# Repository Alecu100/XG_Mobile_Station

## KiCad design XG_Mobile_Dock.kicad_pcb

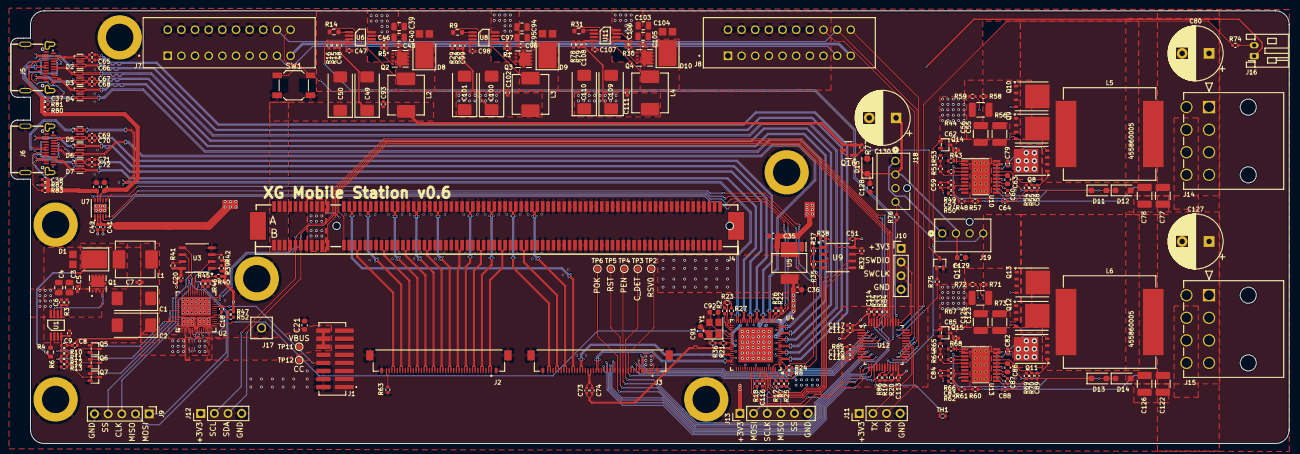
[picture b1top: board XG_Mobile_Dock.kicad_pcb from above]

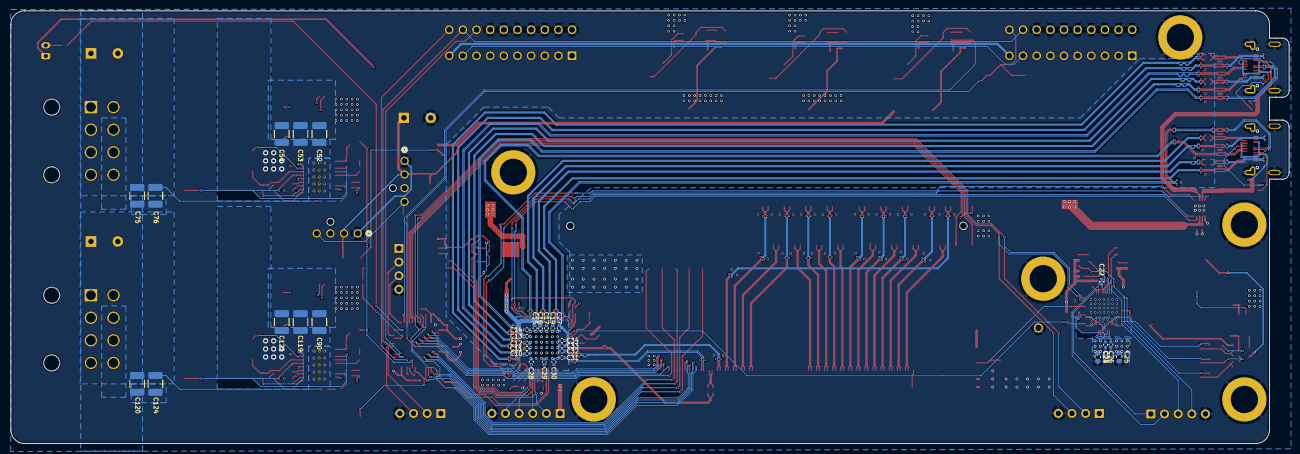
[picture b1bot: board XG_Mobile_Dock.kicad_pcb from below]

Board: 6 copper layers, 237.9 x 80.5 mm, 300 parts (32 on the bottom side), 227 nets.

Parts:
C1, C2, C49, C50, C100, C101, C109, C110: 47µF; CP_EIA-7343-43_Kemet-X
C3, C4, C39, C40, C94, C95, C103, C104: 22µF; C_0805_2012Metric
C5, C7, C10, C11, C12, C13, C14, C16, C17, C20, C27, C28, C29, C30, C31, C33, C34, C43, C51, C58, C65, C66, C67, C68, C69, C70, C71, C72, C73, C74, C79, C82, C89, C93, C96, C102, C105, C111, C112, C113, C114: 0.1µF; C_0402_1005Metric
C6, C9, C46, C47, C60, C64, C87, C88, C97, C98, C106, C107: 1000pF; C_0402_1005Metric
C8, C48, C57, C83, C99, C108: 100pF; C_0402_1005Metric
C15, C19, C32, C59, C84: 0.01µF; C_0402_1005Metric
C18: 220pF; C_0402_1005Metric
C21, C35: 1µF; C_0603_1608Metric
C22, C23, C26: 10µF; C_0402_1005Metric
C24, C25: 10µF; C_0603_1608Metric
C36: 4.7μF; C_0603_1608Metric
C37, C38, C41, C42: 0.1μF; C_0402_1005Metric
C44, C45: 22μF; C_0603_1608Metric
C52, C53, C54, C55, C56, C90, C119, C121, C123, C125: 10µF; C_1210_3225Metric_Pad1.33x2.70mm_HandSolder
C62, C85, C116, C118: 1µF; C_0402_1005Metric
C63, C86: 4.7µF; C_0603_1608Metric
C75, C76, C77, C78, C120, C122, C124, C126: 47µF; C_1210_3225Metric_Pad1.33x2.70mm_HandSolder
C80, C127, C130: 470µF; CP_Radial_D10.0mm_P5.00mm
C91, C92: 18pF; C_0603_1608Metric
C115: 10nF; C_0402_1005Metric
C117: 4.7µF; C_0402_1005Metric
C128, C129: 0.1µF; C_0603_1608Metric
D1, D8, D9, D10: PDS1040L-13; D_PowerDI-5
D2, D3, D4, D5, D6, D7: H5VU25U; AZ1045-04F
D11, D12, D13, D14: D_SOD-123F
D15: 1N4007; D_SOD-123F
H1, H2, H3, H4, H5, H6: Hole_200mil
J1: 5-1775443-8
J2, J3: 20455-040E-76
J4: 3-2362375-4; CONN-SMD_164P-P1.00-V_3133
J5, J6: USB_C_Receptacle; USB-C-SMD_TYPE-C-24P-QT
J7, J8: Conn_02x10_Odd_Even; 5-5530843-0
J9: Conn_01x05; PinHeader_1x05_P2.54mm_Vertical
J10: SWD; PinHeader_1x04_P2.54mm_Vertical
J11: UART; PinHeader_1x04_P2.54mm_Vertical
J12: I2C1; PinHeader_1x04_P2.54mm_Vertical
J13: Conn_01x06; PinHeader_1x06_P2.54mm_Vertical
J14, J15: Conn_02x04_Top_Bottom; CON_455860005_MOL
J16: JST_PH_S2B-PH-K_1x02_P2.00mm_Horizontal
J17: 8730; KEYSTONE_8730
J18, J19: CONN_SD-47053-001_H10p00_MOL
L1, L2, L3, L4: 10µH; L_Abracon_ASPI-0630LR
L5, L6: 10µH; L_Vishay_IHLP-6767
Q1, Q2, Q3, Q4: AON7403; TRANS_AON7403
Q5, Q6, Q7, Q14, Q15, Q17: 2N7002W; SOT-323-3_L2.0-W1.3-P1.30-LS2.1-BR
Q8, Q11: CSD18563Q5A; TDSON-8-1
Q9, Q10, Q12, Q13: CSD18532Q5B; TDSON-8-1
Q16: AO3401A; SOT-23
R1, R3, R30, R74: 47k; R_0402_1005Metric
R2, R7, R8, R21, R22, R23, R33, R34, R47, R48, R61, R63, R77, R85: 10k; R_0402_1005Metric
R4: 49.9k; R_0402_1005Metric
R5: 68k; R_0402_1005Metric
R6, R9, R14, R31: 270; R_0603_1608Metric
R10, R12, R49, R66: 3.3k; R_0402_1005Metric
R11: 1.2k; R_0402_1005Metric
R13: 8.2k; R_0402_1005Metric
R15, R55, R70: 33k; R_0402_1005Metric
R16, R29: 3.9k; R_0402_1005Metric
R17, R18, R19, R20, R32, R35, R37, R38, R39, R40, R41, R42, R45, R46: 4.7k; R_0402_1005Metric
R24, R25, R26, R27, R43, R52, R54, R68, R69, R86: 100k; R_0402_1005Metric
R28, R79: 12k; R_0402_1005Metric
R36: 2.4k; R_0402_1005Metric
R44, R67: 7.5k; R_0402_1005Metric
R50, R62: 680; R_0402_1005Metric
R51, R64: 24k; R_0402_1005Metric
R53, R65, R84: 1k; R_0402_1005Metric
R56, R73: 0.005; R_1210_3225Metric_Pad1.30x2.65mm_HandSolder
R57, R60: 49.9; R_0402_1005Metric
R58, R59, R71, R72, R75: 100; R_0402_1005Metric
R76: 330; R_0402_1005Metric
R78: 20k; R_0402_1005Metric
R80, R81, R82, R83: 22k; R_0402_1005Metric
SW1: SW_Push; SW_SPST_SKQG_WithStem
TH1: NCP15WF104F03RC; R_0402_1005Metric
TP2, TP3, TP4, TP5, TP6, TP11, TP12: TestPoint_Small; TestPoint_Pad_D1.0mm
U1, U6, U8, U11: LM3489MMX/NOPB; LM3489QMM-NOPB
U2: TPS65987DDHRSHR
U3, U9: MX25L8006EM1I-12G
U4: VL822-QFN76
U5: AP7361-10ER-13; SOT230P700X180-4N
U7: TPS2003CDRCR; DRC10_1P65X2P40_TEX
U10, U13: LM5117PMHX/NOPB; PWP0020A_N
U12: STM32F030C8Tx; LQFP-48_7x7mm_P0.5mm
Y1: 25MHz; Crystal_SMD_3225-4Pin_3.2x2.5mm

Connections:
+3V3: C14.1, C15.1, C26.1, C28.1, C30.1, C34.1, C35.1, C51.1, C108.1, C109.1, C110.1, C111.1, C112.1, C113.1, C114.1, C115.1, C117.1, C118.1, J3.1 (+3.3V), J3.2 (+3.3V), J3.3 (+3.3V), J3.4 (+3.3V), J4.A9, J4.A10, J4.B8, J4.B10, J10.1, J11.1, J12.1, J13.1, L4.2, R2.2, R7.1, R8.2, R18.2, R19.1, R20.1, R22.1, R23.1, R24.2, R25.2, R26.1, R27.1, R32.1, R33.1, R34.1, R35.1, R37.1, R38.1, R78.1, R85.2, R86.2, U2.5 (VIN_3V3), U4.17 (VCC33I), U4.24 (VCC33I), U4.46 (VCC33I), U4.62 (VCC33I), U4.73 (VCC33I), U5.3 (IN), U9.8 (VCC), U12.1 (VDD), U12.9 (VDDA), U12.24 (VDD), U12.48 (VDD)
+5V: C41.1, C42.1, C99.1, C100.1, C101.1, C102.1, J16.1, L3.2, R28.1, U7.2 (IN), U7.3 (IN)
+12V: C48.1, C49.1, C50.1, C93.1, J4.A2, J4.A3, J4.B1, J4.B2, J4.B3, L2.2, Q16.2 (S), R15.1, R77.1
+20V: C3.1, C4.1, C5.1, C6.1, C39.1, C40.1, C43.1, C46.1, C52.1, C53.1, C54.1, C55.1, C56.1, C79.2, C82.2, C90.1, C94.1, C95.1, C96.1, C97.1, C103.1, C104.1, C105.1, C106.1, C119.1, C121.1, C123.1, C125.1, J7.1, J7.3, J7.5, J7.7, J7.9, J7.11, J7.13, J7.15, J8.1, J8.3, J8.5, J8.7, J8.9, J8.11, J8.13, J8.15, Q1.1, Q2.1, Q3.1, Q4.1, Q8.5 (D), Q11.5 (D), R1.1, R3.1, R5.1, R30.1, R43.1, R68.1, U1.8 (VIN), U6.8 (VIN), U8.8 (VIN), U10.20 (VIN), U11.8 (VIN), U13.20 (VIN)
/12V_EN: U6.3 (EN), U12.38 (PA15)
/AC_LOSS: J3.15 (P_AC_LOSS), U12.14 (PA4)
/CC: C18.1, J1.13 (CC), TP12.1, U2.24 (C_CC1)
/CLKN: J3.30 (PCIE_CLKN), J4.A14
/CLKP: J3.31 (PCIE_CLKP), J4.A13
/CLKREQ#: J4.B12, U12.42 (PB6)
/CON_DET: J3.11 (CON_DET), TP3.1, U12.10 (PA0)
/C_DN: J3.21 (USB_DM), U4.56 (HSD0–)
/C_DP: J3.22 (USB_DP), U4.55 (HSD0+)
/C_RXN: J3.28 (USB_TXP), U4.52 (SSRX0–)
/C_RXP: J3.27 (USB_TXN), U4.53 (SSRX0+)
/C_TXN: C74.2, J3.24 (USB_RXN)
/C_TXP: C73.2, J3.25 (USB_RXP)
/DET: J2.40 (CON_DET_TOWER#), R63.1
/HP_SHDN#: Q14.1 (G), Q15.1 (G), U12.20 (PB2)
/HSI0N: J2.34 (PCIE_RXN0), J4.A17
/HSI0P: J2.35 (PCIE_RXP0), J4.A16
/HSI1N: J2.28 (PCIE_RXN1), J4.A22
/HSI1P: J2.29 (PCIE_RXP1), J4.A21
/HSI2N: J2.22 (PCIE_RXN2), J4.A26
/HSI2P: J2.23 (PCIE_RXP2), J4.A25
/HSI3N: J2.16 (PCIE_RXN3), J4.A30
/HSI3P: J2.17 (PCIE_RXP3), J4.A29
/HSI4N: J2.10 (PCIE_RXN4), J4.A36
/HSI4P: J2.11 (PCIE_RXP4), J4.A35
/HSI5N: J2.4 (PCIE_RXN5), J4.A40
/HSI5P: J2.5 (PCIE_RXP5), J4.A39
/HSI6N: J3.39 (PCIE_RXN6), J4.A44
/HSI6P: J3.40 (PCIE_RXP6), J4.A43
/HSI7N: J3.33 (PCIE_RXN7), J4.A48
/HSI7P: J3.34 (PCIE_RXP7), J4.A47
/HSO0N: J2.37 (PCIE_TXN0), J4.B15
/HSO0P: J2.38 (PCIE_TXP0), J4.B14
/HSO1N: J2.31 (PCIE_TXN1), J4.B20
/HSO1P: J2.32 (PCIE_TXP1), J4.B19
/HSO2N: J2.25 (PCIE_TXN2), J4.B24
/HSO2P: J2.26 (PCIE_TXP2), J4.B23
/HSO3N: J2.19 (PCIE_TXN3), J4.B28
/HSO3P: J2.20 (PCIE_TXP3), J4.B27
/HSO4N: J2.13 (PCIE_TXN4), J4.B34
/HSO4P: J2.14 (PCIE_TXP4), J4.B33
/HSO5N: J2.7 (PCIE_TXN5), J4.B38
/HSO5P: J2.8 (PCIE_TXP5), J4.B37
/HSO6N: J2.1 (PCIE_TXN6), J4.B42
/HSO6P: J2.2 (PCIE_TXP6), J4.B41
/HSO7N: J3.36 (PCIE_TXN7), J4.B46
/HSO7P: J3.37 (PCIE_TXP7), J4.B45
/LED_RED#: J3.7 (LED_R), U12.4 (PC15)
/LED_WHITE#: J3.6 (LED_W), U12.3 (PC14)
/LOCK_DET: J3.9 (CON_SW1_DET), U12.5 (PF0)
/LOCK_SW: J3.5 (LOCK_SW), U12.2 (PC13)
/MCU/FAN_ON: R75.1, U12.33 (PA12)
/MCU/FAN_PWM: R76.1, U12.39 (PB3)
/MCU/RX: J11.3, U12.31 (PA10)
/MCU/SCL2: R19.2, U12.21 (PB10)
/MCU/SDA2: R20.2, U12.22 (PB11)
/MCU/SWCLK: J10.3, U12.37 (PA14)
/MCU/SWDIO: J10.2, U12.34 (PA13)
/MCU/TX: J11.2, U12.30 (PA9)
/MCU/~CASE_LED: R74.1, U12.36 (PF7)
/MCU_IRQ#: J3.16 (MCU_IRQ#), U12.15 (PA5)
/PERST#: J4.A11, U12.41 (PB5)
/PWREN#: J3.12 (PWR_EN#), TP4.1, U12.11 (PA1)
/PWROK: J3.14 (PWROK), TP6.1, U12.13 (PA3)
/PWR_SW: J7.20, R85.1, SW1.1, U12.7 (NRST)
/PWR_SW_OUT: J8.20, U12.25 (PB12)
/Power 12V (1)/VCC: C63.1, D11.2 (A), D12.1 (K), U10.3 (RES), U10.16 (VCC)
/Power 12V (1)/VOUT_12V: C75.1, C76.1, C77.1, C78.1, C80.1, D12.2 (A), J14.1, J14.2, J14.3, L5.2, R57.2
/Power 12V (2)/VCC: C86.1, D13.2 (A), D14.1 (K), U13.3 (RES), U13.16 (VCC)
/Power 12V (2)/VOUT_12V: C120.1, C122.1, C124.1, C126.1, C127.1, D14.2 (A), J15.1, J15.2, J15.3, L6.2, R60.2
/RST#: J3.13 (RST#), TP5.1, U12.12 (PA2)
/RSV0: J3.10, TP2.1, U12.6 (PF1)
/SCL: J3.19 (SMB1_CLK), J4.B5, J12.2, R33.2, U2.27 (I2C1_SCL), U4.66 (GPIO8/SMCLK), U12.45 (PB8)
/SDA: J3.18 (SMB1_DAT), J4.B6, J12.3, R34.2, U2.28 (I2C1_SDA), U4.65 (GPIO7/SMDAT), U12.46 (PB9)
/SYS_3V3: J7.19, J8.19
/SYS_DET: J8.16, U12.27 (PB14)
/SYS_ON: J7.18, J8.18, U12.26 (PB13)
/USB C DFPs/USB_DFP0_D1N: D3.2 (I/O_2), D3.9 (NC), J5.A7 (D-), U4.10 (HSD1–)
/USB C DFPs/USB_DFP0_D1P: D3.1 (I/O_1), D3.10 (NC), J5.A6 (D+), U4.9 (HSD1+)
/USB C DFPs/USB_DFP0_D2N: D4.5 (I/O_4), D4.6 (NC), J5.B7 (D-), U4.19 (HSD2–)
/USB C DFPs/USB_DFP0_D2P: D4.4 (I/O_3), D4.7 (NC), J5.B6 (D+), U4.18 (HSD2+)
/USB C DFPs/USB_DFP0_RX1N: D2.5 (I/O_4), D2.6 (NC), J5.B10 (RX1-), U4.7 (SSRX1–)
/USB C DFPs/USB_DFP0_RX1P: D2.4 (I/O_3), D2.7 (NC), J5.B11 (RX1+), U4.6 (SSRX1+)
/USB C DFPs/USB_DFP0_RX2N: D4.1 (I/O_1), D4.10 (NC), J5.A10 (RX2-), U4.15 (SSRX2+)
/USB C DFPs/USB_DFP0_RX2P: D4.2 (I/O_2), D4.9 (NC), J5.A11 (RX2+), U4.16 (SSRX2–)
/USB C DFPs/USB_DFP0_TX1N: C66.1, D2.2 (I/O_2), D2.9 (NC), J5.A3 (TX1-)
/USB C DFPs/USB_DFP0_TX1P: C65.1, D2.1 (I/O_1), D2.10 (NC), J5.A2 (TX1+)
/USB C DFPs/USB_DFP0_TX2N: C67.1, D3.4 (I/O_3), D3.7 (NC), J5.B3 (TX2-)
/USB C DFPs/USB_DFP0_TX2P: C68.1, D3.5 (I/O_4), D3.6 (NC), J5.B2 (TX2+)
/USB C DFPs/USB_DFP0_VBUS: C37.1, C44.1, J5.A4 (VBUS), J5.A9 (VBUS), J5.B4 (VBUS), J5.B9 (VBUS), R80.2, R81.1, U7.8 (OUT2)
/USB C DFPs/USB_DFP1_D1N: D6.5 (I/O_4), D6.6 (NC), J6.A7 (D-), U4.23 (HSD3–)
/USB C DFPs/USB_DFP1_D1P: D6.4 (I/O_3), D6.7 (NC), J6.A6 (D+), U4.22 (HSD3+)
/USB C DFPs/USB_DFP1_D2N: D5.1 (I/O_1), D5.10 (NC), J6.B7 (D-), U4.38 (HSD4–)
/USB C DFPs/USB_DFP1_D2P: D5.2 (I/O_2), D5.9 (NC), J6.B6 (D+), U4.37 (HSD4+)
/USB C DFPs/USB_DFP1_RX1N: D6.2 (I/O_2), D6.9 (NC), J6.B10 (RX1-), U4.29 (SSRX3–)
/USB C DFPs/USB_DFP1_RX1P: D6.1 (I/O_1), D6.10 (NC), J6.B11 (RX1+), U4.28 (SSRX3+)
/USB C DFPs/USB_DFP1_RX2N: D7.4 (I/O_3), D7.7 (NC), J6.A10 (RX2-), U4.34 (SSRX4+)
/USB C DFPs/USB_DFP1_RX2P: D7.5 (I/O_4), D7.6 (NC), J6.A11 (RX2+), U4.35 (SSRX4–)
/USB C DFPs/USB_DFP1_TX1N: C70.1, D5.5 (I/O_4), D5.6 (NC), J6.A3 (TX1-)
/USB C DFPs/USB_DFP1_TX1P: C69.1, D5.4 (I/O_3), D5.7 (NC), J6.A2 (TX1+)
/USB C DFPs/USB_DFP1_TX2N: C71.1, D7.1 (I/O_1), D7.10 (NC), J6.B3 (TX2-)
/USB C DFPs/USB_DFP1_TX2P: C72.1, D7.2 (I/O_2), D7.9 (NC), J6.B2 (TX2+)
/USB C DFPs/USB_DFP1_VBUS: C38.1, C45.1, J6.A4 (VBUS), J6.A9 (VBUS), J6.B4 (VBUS), J6.B9 (VBUS), R82.2, R83.1, U7.9 (OUT1)
/USB Hub/+1V0: C10.1, C11.1, C12.1, C13.1, C16.1, C17.1, C19.1, C27.1, C29.1, C31.1, C32.1, C33.1, C36.1, U4.5 (VCC10I), U4.8 (VCC10I), U4.11 (VDD), U4.14 (VCC10I), U4.27 (VCC10I), U4.30 (VDD), U4.33 (VCC10I), U4.36 (VCC10I), U4.48 (VDD), U4.51 (VCC10I), U4.54 (VCC10I), U4.67 (VDD), U5.2 (OUT_1), U5.4 (OUT_2)
/USB Hub/RESET: C116.1, R18.1, U4.68 (RESET#)
/USB Hub/REXT: R21.1, U4.47 (REXT)
/USB Hub/SPI_CLK: J13.3, U4.70 (USBLED2/SPICK), U9.6 (SCLK)
/USB Hub/SPI_MISO: J13.4, R38.2, U4.71 (USBLED3/SPISO), U9.2 (SO/SIO1)
/USB Hub/SPI_MOSI: J13.2, U4.69 (USBLED1/SPISI), U9.5 (SI/SIO0)
/USB Hub/SPI_SS: J13.5, R37.2, U4.72 (USBLED4/SPICS), U9.1 (~CS)
/USB Hub/SSTX0+: C73.1, U4.50 (SSTX0+)
/USB Hub/SSTX0-: C74.1, U4.49 (SSTX0–)
/USB Hub/SSTX1+: C65.2, U4.3 (SSTX1+)
/USB Hub/SSTX1-: C66.2, U4.4 (SSTX1–)
/USB Hub/SSTX2+: C67.2, U4.12 (SSTX2+)
/USB Hub/SSTX2-: C68.2, U4.13 (SSTX2–)
/USB Hub/SSTX3+: C69.2, U4.25 (SSTX3+)
/USB Hub/SSTX3-: C70.2, U4.26 (SSTX3–)
/USB Hub/SSTX4+: C71.2, U4.31 (SSTX4+)
/USB Hub/SSTX4-: C72.2, U4.32 (SSTX4–)
/USB Hub/TESTEN: R17.2, U4.74 (TESTEN)
/USB Hub/USBOC0: R2.1, U4.41 (USBOC0)
/USB Hub/USB_DFP0_EN: R24.1, U4.2 (USBPE1), U7.5 (EN2)
/USB Hub/USB_DFP0_FLT: R7.2, R8.1, U4.1 (USBOC1), U4.75 (USBOC2), U7.6 (*FLT2)
/USB Hub/USB_DFP1_EN: R25.1, U4.76 (USBPE2)
/USB Hub/USB_DFP2_EN: R26.2, U4.21 (USBPE3), U7.4 (EN1)
/USB Hub/USB_DFP2_FLT: R22.2, R23.2, U4.20 (USBOC3), U4.40 (USBOC4), U7.10 (*FLT1)
/USB Hub/USB_DFP3_EN: R27.2, U4.39 (USBPE4)
/USB Hub/VBUSDET: U2.16 (GPIO0), U4.43 (VBUSDET0)
/USB Hub/XI: C91.1, U4.45 (USB3XI), Y1.1
/USB Hub/XO: C92.1, U4.44 (USB3XO), Y1.3
/USB PD Charger/BOOT: R47.2, R52.1, U2.6 (ADCIN1)
/USB PD Charger/DRAIN1: U2.8 (DRAIN1), U2.15 (DRAIN1), U2.19 (DRAIN1), U2.58 (DRAIN1)
/USB PD Charger/DRAIN2: U2.7 (DRAIN2), U2.52 (DRAIN2), U2.56 (DRAIN2), U2.57 (DRAIN2)
/USB PD Charger/LDO_3V3: C20.1, C23.1, R39.1, R40.1, R41.1, R42.1, R45.2, R46.2, R47.1, U2.9 (LDO_3V3), U3.8 (VCC)
/USB PD Charger/PDO_1: Q7.1 (G), U2.43 (GPIO15)
/USB PD Charger/PDO_2: Q6.1 (G), U2.49 (GPIO17)
/USB PD Charger/PDO_3: Q5.1 (G), U2.54 (GPIO20)
/USB PD Charger/SPI_CLK: J9.3, U2.38 (SPI_CLK), U3.6 (SCLK)
/USB PD Charger/SPI_MISO: J9.2, R40.2, U2.36 (SPI_MISO), U3.2 (SO/SIO1)
/USB PD Charger/SPI_MOSI: J9.1, U2.37 (SPI_MOSI), U3.5 (SI/SIO0)
/USB PD Charger/SPI_SS: J9.4, R39.2, U2.39 (SPI_SS), U3.1 (~CS)
/VBUS: C21.1, J1.9 (VBUS), J1.10 (VBUS), J1.11 (VBUS), TP11.1, U2.3 (VBUS2), U2.4 (VBUS2), U2.13 (VBUS1), U2.14 (VBUS1)
/WAKE#: J4.B11, U12.40 (PB4)
GND: C1.2, C2.2, C3.2, C4.2, C5.2, C7.2, C9.2, C10.2, C11.2, C12.2, C13.2, C14.2, C15.2, C16.2, C17.2, C18.2, C19.2, C20.2, C21.2, C22.2, C23.2, C24.2, C25.2, C26.2, C27.2, C28.2, C29.2, C30.2, C31.2, C32.2, C33.2, C34.2, C35.2, C36.2, C37.2, C38.2, C39.2, C40.2, C41.2, C42.2, C43.2, C44.2, C45.2, C47.2, C49.2, C50.2, C51.2, C52.2, C53.2, C54.2, C55.2, C56.2, C62.1, C63.2, C64.1, C75.2, C76.2, C77.2, C78.2, C79.1, C80.2, C82.1, C85.1, C86.2, C88.1, C90.2, C91.2, C92.2, C93.2, C94.2, C95.2, C96.2, C98.2, C100.2, C101.2, C102.2, C103.2, C104.2, C105.2, C107.2, C109.2, C110.2, C111.2, C112.2, C113.2, C114.2, C115.2, C116.2, C117.2, C118.2, C119.2, C120.2, C121.2, C122.2, C123.2, C124.2, C125.2, C126.2, C127.2, C128.2, C129.2, C130.2, D1.2 (A), D2.3 (GND), D2.8 (GND), D3.3 (GND), D3.8 (GND), D4.3 (GND), D4.8 (GND), D5.3 (GND), D5.8 (GND), D6.3 (GND), D6.8 (GND), D7.3 (GND), D7.8 (GND), D8.2 (A), D9.2 (A), D10.2 (A), D15.2 (A), H1.1, H2.1, H3.1, H4.1, H5.1, H6.1, J1.14 (GND), J1.15 (GND), J1.16 (GND), J2.3 (GND), J2.6 (GND), J2.9 (GND), J2.12 (GND), J2.15 (GND), J2.18 (GND), J2.21 (GND), J2.24 (GND), J2.27 (GND), J2.30 (GND), J2.33 (GND), J2.36 (GND), J2.39 (GND), J2.S1 (SHIELD), J2.S2 (SHIELD), J2.S3 (SHIELD), J2.S4 (SHIELD), J3.17 (GND), J3.20 (GND), J3.23 (GND), J3.26 (GND), J3.29 (GND), J3.32 (GND), J3.35 (GND), J3.38 (GND), J3.S1 (SHIELD), J3.S2 (SHIELD), J3.S3 (SHIELD), J3.S4 (SHIELD), J4.A4, J4.A12, J4.A15, J4.A18, J4.A20, J4.A23, J4.A24, J4.A27, J4.A28, J4.A31, J4.A34, J4.A37, J4.A38, J4.A41, J4.A42, J4.A45, J4.A46, J4.A49, J4.A51, J4.A54, J4.A55, J4.A58, J4.A59, J4.A62, J4.A63, J4.A66, J4.A67, J4.A70, J4.A71, J4.A74, J4.A75, J4.A78, J4.A79, J4.A82, J4.B4, J4.B7, J4.B13, J4.B16, J4.B18, J4.B21, J4.B22, J4.B25, J4.B26, J4.B29, J4.B32, J4.B35, J4.B36, J4.B39, J4.B40, J4.B43, J4.B44, J4.B47, J4.B49, J4.B52, J4.B53, J4.B56, J4.B57, J4.B60, J4.B61, J4.B64, J4.B65, J4.B68, J4.B69, J4.B72, J4.B73, J4.B76, J4.B77, J4.B80, J5.A1 (GND), J5.A12 (GND), J5.B1 (GND), J5.B12 (GND), J5.S1 (SHIELD), J6.A1 (GND), J6.A12 (GND), J6.B1 (GND), J6.B12 (GND), J6.S1 (SHIELD), J7.2, J7.4, J7.6, J7.8, J7.10, J7.12, J7.14, J7.16, J8.2, J8.4, J8.6, J8.8, J8.10, J8.12, J8.14, J9.5, J10.4, J11.4, J12.4, J13.6, J14.4, J14.5, J14.6, J14.7, J14.8, J15.4, J15.5, J15.6, J15.7, J15.8, J17.1, J18.1, J19.1, Q5.2 (S), Q6.2 (S), Q7.2 (S), Q14.2 (S), Q15.2 (S), Q17.2 (S), R13.2, R16.1, R17.1, R29.1, R36.2, R44.1, R50.2, R52.2, R53.2, R56.2, R59.1, R62.2, R63.2, R65.2, R67.1, R72.1, R73.2, R79.2, R84.1, SW1.2, TH1.2, U1.2 (GND), U1.6 (PGND), U2.10 (ADCIN2), U2.20 (GND), U2.25 (PP_CABLE), U2.44 (HRESET), U2.45 (GND), U2.46 (GND), U2.47 (GND), U2.51 (GND), U2.59 (GND), U3.4 (GND), U4.77 (EP), U5.1 (GND), U6.2 (GND), U6.6 (PGND), U7.1 (GND), U7.11 (EPAD), U8.2 (GND), U8.6 (PGND), U9.4 (GND), U10.6 (AGND), U10.14 (PGND), U10.21 (EP), U11.2 (GND), U11.6 (PGND), U12.8 (VSSA), U12.23 (VSS), U12.47 (VSS), U13.6 (AGND), U13.14 (PGND), U13.21 (EP), Y1.2, Y1.4
unnamed: C59.1, R49.1
unnamed: C84.1, R66.1
unnamed: D1.1 (K), L1.1, Q1.5_8, R6.2
unnamed: D8.1 (K), L2.1, Q2.5_8, R14.2
unnamed: D9.1 (K), L3.1, Q3.5_8, R9.2
unnamed: D10.1 (K), L4.1, Q4.5_8, R31.2
unnamed: C58.1, D11.1 (K), U10.19 (HB)
unnamed: C89.1, D13.1 (K), U13.19 (HB)
unnamed: C128.1, C129.1, C130.1, D15.1 (K), J18.2, J19.2, Q16.3 (D)
unnamed: J5.A5 (CC1), R80.1
unnamed: J5.B5 (CC2), R81.2
unnamed: J6.A5 (CC1), R82.1
unnamed: J6.B5 (CC2), R83.2
unnamed: J7.17, J8.17
unnamed: J16.2, R74.2
unnamed: J18.4, J19.4, R76.2
unnamed: Q5.3 (D), R10.2, R11.1
unnamed: Q6.3 (D), R11.2, R12.1
unnamed: Q7.3 (D), R12.2, R13.1
unnamed: Q8.4 (G), U10.18 (HO)
unnamed: C58.2, L5.1, Q8.1 (S), Q8.2 (S), Q8.3 (S), Q9.5 (D), Q10.5 (D), R55.2, U10.17 (SW)
unnamed: Q9.4 (G), Q10.4 (G), U10.15 (LO)
unnamed: Q9.1 (S), Q9.2 (S), Q9.3 (S), Q10.1 (S), Q10.2 (S), Q10.3 (S), R56.1, R58.1
unnamed: Q11.4 (G), U13.18 (HO)
unnamed: C89.2, L6.1, Q11.1 (S), Q11.2 (S), Q11.3 (S), Q12.5 (D), Q13.5 (D), R70.2, U13.17 (SW)
unnamed: Q12.4 (G), Q13.4 (G), U13.15 (LO)
unnamed: Q12.1 (S), Q12.2 (S), Q12.3 (S), Q13.1 (S), Q13.2 (S), Q13.3 (S), R71.1, R73.1
unnamed: Q14.3 (D), R43.2, R44.2, U10.1 (UVLO)
unnamed: Q15.3 (D), R67.2, R68.2, U13.1 (UVLO)
unnamed: Q16.1 (G), Q17.3 (D), R77.2
unnamed: Q17.1 (G), R75.2
unnamed: R21.2, R36.1
unnamed: R48.2, R57.1
unnamed: R51.2, R53.1
unnamed: R54.2, R55.1
unnamed: R60.1, R61.2
unnamed: R64.2, R65.1
unnamed: R69.2, R70.1
unnamed: C6.2, R3.2, U1.5 (ADJ)
unnamed: C8.2, C9.1, R4.2, R10.1, U1.4 (FB)
unnamed: R6.1, U1.1 (ISENSE)
unnamed: Q1.4, U1.7 (PGATE)
unnamed: R46.1, U2.32 (I2C2_SCL)
unnamed: R45.1, U2.33 (I2C2_SDA)
unnamed: C22.1, U2.35 (LDO_1V8)
unnamed: R41.2, U3.7 (~HOLD)
unnamed: R42.2, U3.3 (~WP)
unnamed: C46.2, R5.2, U6.5 (ADJ)
unnamed: C47.1, C48.2, R15.2, R16.2, U6.4 (FB)
unnamed: R14.1, U6.1 (ISENSE)
unnamed: Q2.4, U6.7 (PGATE)
unnamed: C97.2, R1.2, U8.5 (ADJ)
unnamed: C98.1, C99.2, R28.2, R29.2, U8.4 (FB)
unnamed: R9.1, U8.1 (ISENSE)
unnamed: Q3.4, U8.7 (PGATE)
unnamed: R32.2, U9.7 (~HOLD)
unnamed: R35.2, U9.3 (~WP)
unnamed: C57.2, C59.2, U10.9 (COMP)
unnamed: C60.2, R58.2, U10.12 (CS)
unnamed: C60.1, R59.2, U10.13 (CSG)
unnamed: C57.1, R48.1, R49.2, R50.1, U10.8 (FB)
unnamed: C64.2, R54.1, U10.11 (RAMP)
unnamed: R51.1, U10.5 (RT)
unnamed: C62.2, U10.4 (SS)
unnamed: C106.2, R30.2, U11.5 (ADJ)
unnamed: C107.1, C108.2, R78.2, R79.1, U11.4 (FB)
unnamed: R31.1, U11.1 (ISENSE)
unnamed: Q4.4, U11.7 (PGATE)
unnamed: R84.2, U12.44 (BOOT0)
unnamed: R86.1, TH1.1, U12.19 (PB1)
unnamed: C83.2, C84.2, U13.9 (COMP)
unnamed: C87.2, R71.2, U13.12 (CS)
unnamed: C87.1, R72.2, U13.13 (CSG)
unnamed: C83.1, R61.1, R62.1, R66.2, U13.8 (FB)
unnamed: C88.2, R69.1, U13.11 (RAMP)
unnamed: R64.1, U13.5 (RT)
unnamed: C85.2, U13.4 (SS)
PP_HV: C1.1, C2.1, C7.1, C8.1, C24.1, C25.1, L1.2, R4.1, U2.1 (PP_HV2), U2.2 (PP_HV2), U2.11 (PP_HV1), U2.12 (PP_HV1)
